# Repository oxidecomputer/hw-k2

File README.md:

# hw-k2

This design provides a PCIe extender that converts from
a U.2 PCIe device connector and provides a x4 PCIe CEM slot.

This is designed to work on *our* gimlet computer sled with a 
sharkfin PCIe riser.  Whether this can be generally used in
other applications is unknown.

This repository includes a 3d-printable encolosure design that
fits in our sled and provides brackets for both of the commonly
used NICs.

[Mechanicals](mech_model)

# Status
The CAD represents a functional design.

# PLM

For the sake of clarity and consistency, the PLM-released files are renamed and
organized in the `plm` directory.

| PLM Name | Repo Name |
| -------------------------------- | --------------------------------------------- |
| 913-0000114_rev1_v1.d356 | gerbers/u2CEM.d356
| 913-0000114_rev1_v1_bom.xlsx | pulled out of the gerber zip
| 913-0000114_rev1_v1_gerbers.zip | gerbers/913-0000114_rev1.zip
| 913-0000114_rev1_v1_odb.zip | gerbers/u2CEM-odb.zip
| 913-0000114_rev1_v1_schematic.pdf | 913-0000114.pdf
| 913-0000114_rev1_v1_stackup.xlsx | stackup-K2-6lyr-FR408HR_rev4_26_MAR_2026.xlsx

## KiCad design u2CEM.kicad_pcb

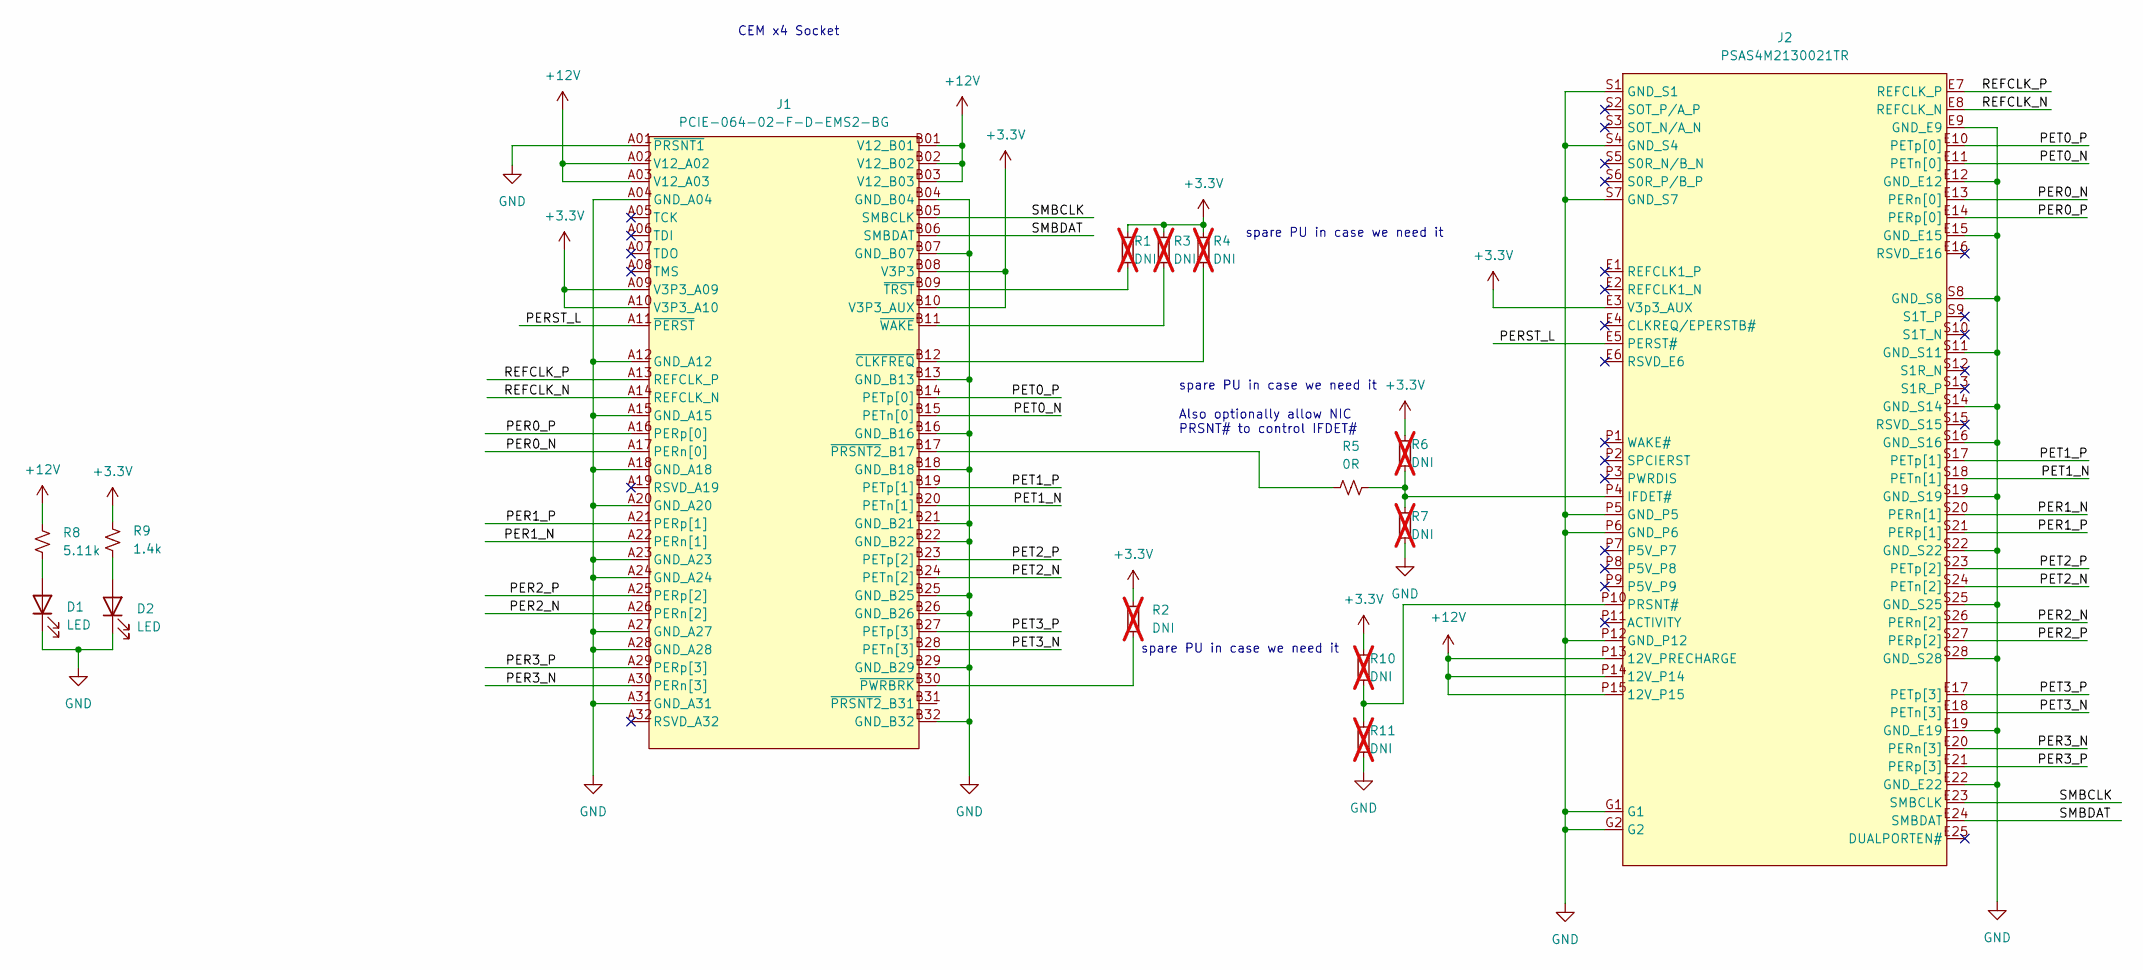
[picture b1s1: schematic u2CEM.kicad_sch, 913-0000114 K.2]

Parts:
D1, D2: LED; LED_0603_1608Metric; MPN LTST-C193KSKT-5A
J1: PCIE-064-02-F-D-EMS2-BG; SAMTEC_PCIE-064-02-X-D-EMS2-BG; MPN PCIE-064-02-F-D-EMS2-BG
J2: PSAS4M2130021TR; MPN PSAS4M2130021TR
R1, R2, R3, R4, R6, R7, R10, R11: DNI; R_0603_1608Metric; not fitted
R5: 0R; R_0603_1608Metric; MPN RC0603JR-070RL
R8: 5.11k; R_0603_1608Metric; MPN RC0603FR-075K11L
R9: 1.4k; R_0603_1608Metric; MPN RC0603FR-071K4L

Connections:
+3.3V: J1.A09 (V3P3_A09), J1.A10 (V3P3_A10), J1.B08 (V3P3), J1.B10 (V3P3_AUX), J2.E3 (V3p3_AUX), R1.1, R2.1, R3.1, R4.1, R6.1, R9.1, R10.1
+12V: J1.A02 (V12_A02), J1.A03 (V12_A03), J1.B01 (V12_B01), J1.B02 (V12_B02), J1.B03 (V12_B03), J2.P13 (12V_PRECHARGE), J2.P14 (12V_P14), J2.P15 (12V_P15), R8.1
/PER0_N: J1.A17 (PERn[0]), J2.E13 (PERn[0])
/PER0_P: J1.A16 (PERp[0]), J2.E14 (PERp[0])
/PER1_N: J1.A22 (PERn[1]), J2.S20 (PERn[1])
/PER1_P: J1.A21 (PERp[1]), J2.S21 (PERp[1])
/PER2_N: J1.A26 (PERn[2]), J2.S26 (PERn[2])
/PER2_P: J1.A25 (PERp[2]), J2.S27 (PERp[2])
/PER3_N: J1.A30 (PERn[3]), J2.E20 (PERn[3])
/PER3_P: J1.A29 (PERp[3]), J2.E21 (PERp[3])
/PERST_L: J1.A11 (~PERST), J2.E5 (PERST#)
/PET0_N: J1.B15 (PETn[0]), J2.E11 (PETn[0])
/PET0_P: J1.B14 (PETp[0]), J2.E10 (PETp[0])
/PET1_N: J1.B20 (PETn[1]), J2.S18 (PETn[1])
/PET1_P: J1.B19 (PETp[1]), J2.S17 (PETp[1])
/PET2_N: J1.B24 (PETn[2]), J2.S24 (PETn[2])
/PET2_P: J1.B23 (PETp[2]), J2.S23 (PETp[2])
/PET3_N: J1.B28 (PETn[3]), J2.E18 (PETn[3])
/PET3_P: J1.B27 (PETp[3]), J2.E17 (PETp[3])
/REFCLK_N: J1.A14 (REFCLK_N), J2.E8 (REFCLK_N)
/REFCLK_P: J1.A13 (REFCLK_P), J2.E7 (REFCLK_P)
/SMBCLK: J1.B05 (SMBCLK), J2.E23 (SMBCLK)
/SMBDAT: J1.B06 (SMBDAT), J2.E24 (SMBDAT)
GND: D1.1 (K), D2.1 (K), J1.A01 (~PRSNT1), J1.A04 (GND_A04), J1.A12 (GND_A12), J1.A15 (GND_A15), J1.A18 (GND_A18), J1.A20 (GND_A20), J1.A23 (GND_A23), J1.A24 (GND_A24), J1.A27 (GND_A27), J1.A28 (GND_A28), J1.A31 (GND_A31), J1.B04 (GND_B04), J1.B07 (GND_B07), J1.B13 (GND_B13), J1.B16 (GND_B16), J1.B18 (GND_B18), J1.B21 (GND_B21), J1.B22 (GND_B22), J1.B25 (GND_B25), J1.B26 (GND_B26), J1.B29 (GND_B29), J1.B32 (GND_B32), J2.E9 (GND_E9), J2.E12 (GND_E12), J2.E15 (GND_E15), J2.E19 (GND_E19), J2.E22 (GND_E22), J2.G1, J2.G2, J2.P5 (GND_P5), J2.P6 (GND_P6), J2.P12 (GND_P12), J2.S1 (GND_S1), J2.S4 (GND_S4), J2.S7 (GND_S7), J2.S8 (GND_S8), J2.S11 (GND_S11), J2.S14 (GND_S14), J2.S16 (GND_S16), J2.S19 (GND_S19), J2.S22 (GND_S22), J2.S25 (GND_S25), J2.S28 (GND_S28), R7.2, R11.2
unnamed: D1.2 (A), R8.2
unnamed: D2.2 (A), R9.2
unnamed: J1.B12 (~CLKFREQ), R4.2
unnamed: J1.B17 (~PRSNT2_B17), R5.1
unnamed: J1.B30 (~PWRBRK), R2.2
unnamed: J1.B09 (~TRST), R1.2
unnamed: J1.B11 (~WAKE), R3.2
unnamed: J2.P4 (IFDET#), R5.2, R6.2, R7.1
unnamed: J2.P10 (PRSNT#), R10.2, R11.1

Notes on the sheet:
CEM x4 Socket
spare PU in case we need it Also optionally allow NIC PRSNT# to control IFDET#
spare PU in case we need it

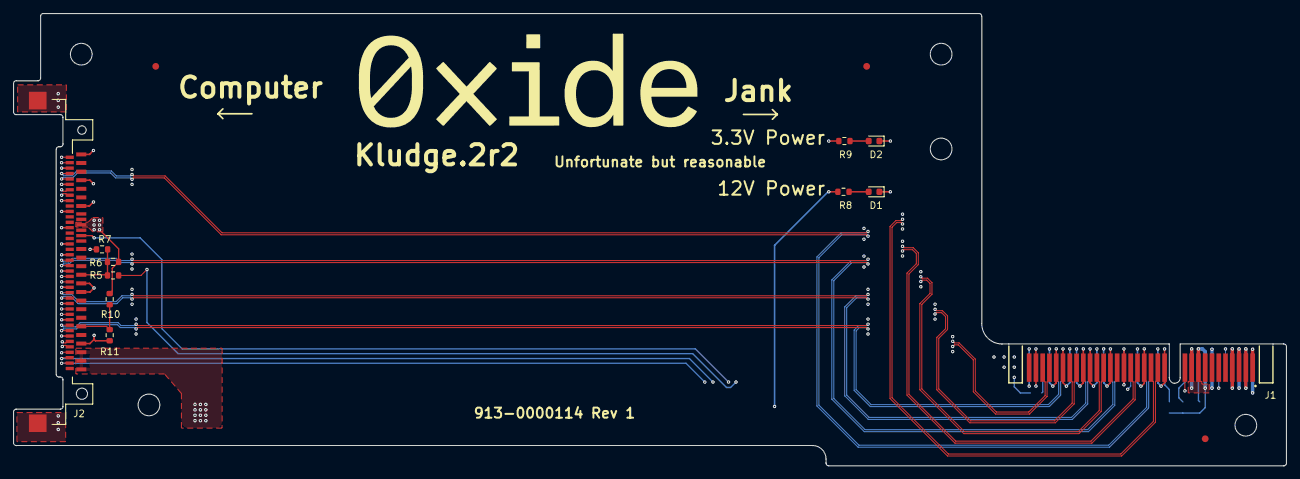
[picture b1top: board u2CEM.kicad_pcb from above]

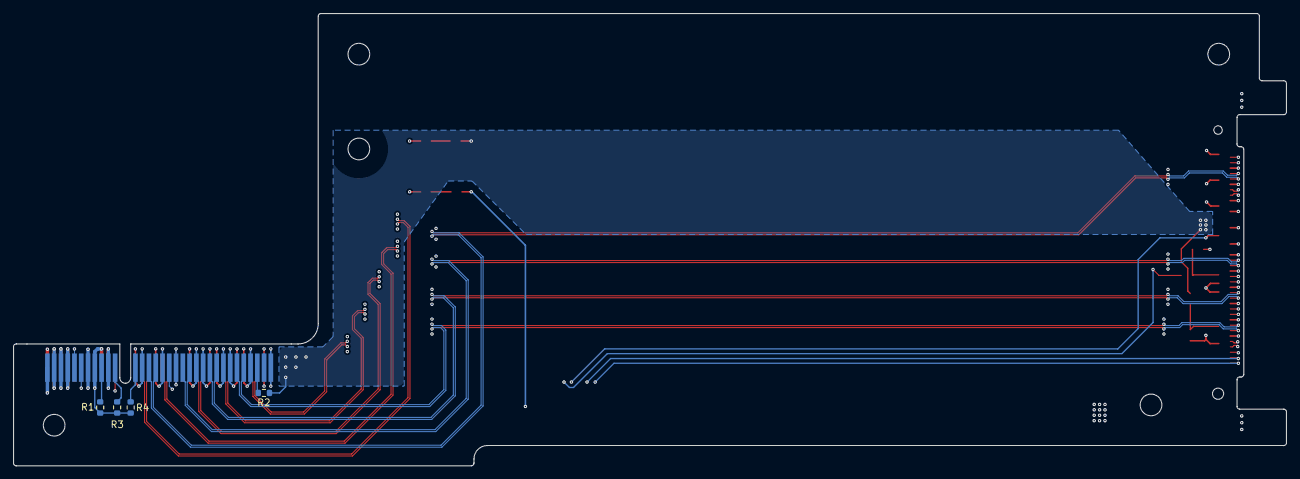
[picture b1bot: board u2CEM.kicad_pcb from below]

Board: 6 copper layers, 188.0 x 66.8 mm, 15 parts (4 on the bottom side), 33 nets.

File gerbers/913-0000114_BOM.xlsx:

Item# | Reference | Qty | DNP | MFG | MPN | Value
1 | D1,D2 | 2 |  | Lite-On Inc. | LTST-C193KSKT-5A | LED
2 | J1 | 1 |  | Samtec | PCIE-064-02-F-D-EMS2-BG | PCIE-064-02-F-D-EMS2-BG
3 | J2 | 1 |  | Amphenol | PSAS4M2130021TR | PSAS4M2130021TR
4 | R5 | 1 |  | Yageo | RC0603JR-070RL | 0R
5 | R8 | 1 |  | Yageo | RC0603FR-075K11L | 5.11k
6 | R9 | 1 |  | Yageo | RC0603FR-071K4L | 1.4k
7 | R1,R2,R3,R4,R6,R7,R10,R11 | 8 | DNP |  |  | DNI

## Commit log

2022-11-04 new version
2022-11-08 fixed outline and DRCs
2022-11-16 deleting old gerbers
2022-11-18 Package sent to tapeout
    final PCB package with updated trace width/spacing based on Ian calculating the required dimensions correctly instead of doing it wrong like I did.
    MCAD design still in flux
2023-02-24 Add license
2023-02-24 restructuring
2023-02-24 nicer render colors
2023-02-24 remove files that are in the release
2023-02-24 Finalized mech model with all hardware
2025-05-09 updating mech model for clearance on Cosmo U.2 guide tabs
2025-05-09 updating STL for the StarTech NIC support Bracket
2026-03-10 initial quote request to Sierra
2026-03-10 adding stackup file and deleting individual gerbers
2026-03-25 adding IPC netlist and fixed stackup file due to another typo
2026-03-26 fixing another typo in the stackup spreadsheet
2026-03-27 adding the PDF of the stackup Sierra wanted based on on-hand materials
2026-04-08 pcba: rev 1 release files
2026-04-14 feedback from Eric
2026-04-14 pcba: rev 1 release files (#5)
